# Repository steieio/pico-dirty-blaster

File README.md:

# Pico Dirty Blaster
USB Blaster adapters for [pico-dirtyJtag](https://github.com/phdussud/pico-dirtyJtag)
Also supports [Drag-n-Drop FPGA programming via UF2](https://steieio.github.io/pico-dirty-blaster/uf2jbc.html)
More documentation [available here](https://steieio.github.io/pico-dirty-blaster/)
You can purchase the PCB from [OSH Park](https://oshpark.com/)
 * [Through Hole PCB design at OSH Park](https://oshpark.com/shared_projects/5RjXdQ8y)

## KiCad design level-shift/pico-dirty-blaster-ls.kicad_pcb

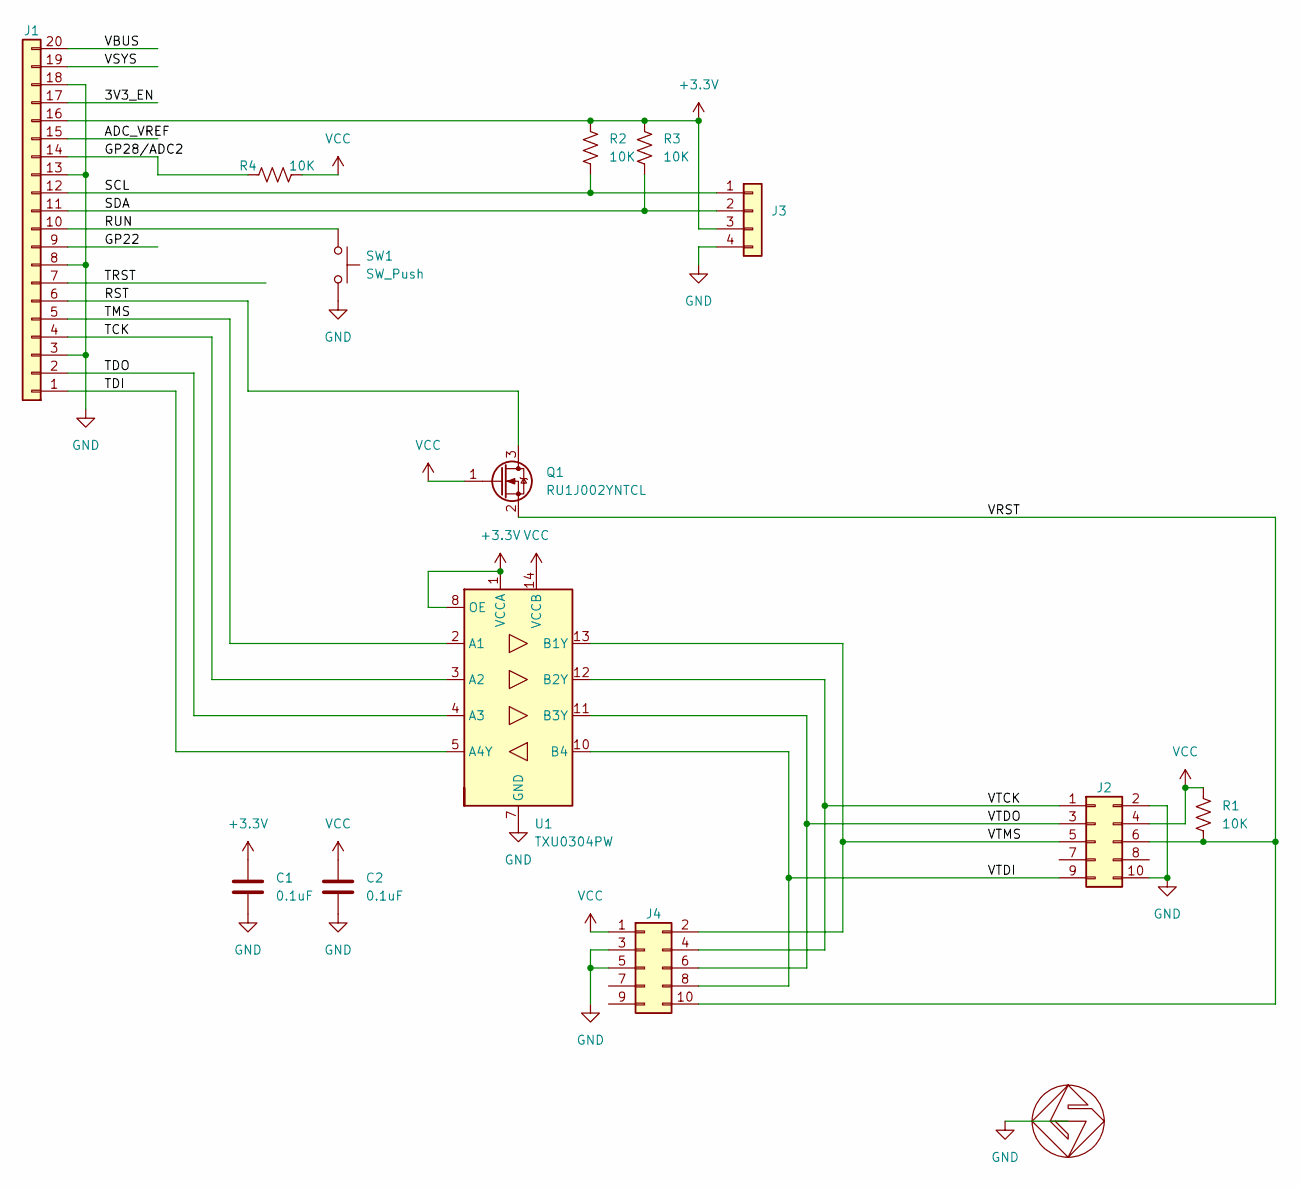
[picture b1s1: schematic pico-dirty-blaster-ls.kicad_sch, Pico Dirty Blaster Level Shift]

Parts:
C1, C2: 0.1uF; C_0603_1608Metric
GS1: GS_logo; gs_logo_200mil
J1: Conn_01x20; Sidecar-20
J2: Conn_02x05_Odd_Even; BHR-10-VSG-SMT_2x05_P2.54mm_Vertical_SMD
J3: Conn_01x04; JST_SH_SM04B-SRSS-TB_1x04-1MP_P1.00mm_Horizontal
J4: Conn_02x05_Odd_Even; PinHeader_2x05_P1.27mm_Vertical_SMD
Q1: RU1J002YNTCL; SOT-323_SC-70
R1, R2, R3, R4: 10K; R_0402_1005Metric
SW1: SW_Push; SW_Push_1P1T_NO_Vertical_Wuerth_434133025816
U1: TXU0304PW; TSSOP-14_4.4x5mm_P0.65mm

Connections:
+3.3V: C1.1, J1.16, J3.3, R2.1, R3.1, U1.1 (VCCA), U1.8 (OE)
/3V3_EN: J1.17
/ADC_VREF: J1.15
/GP22: J1.9
/GP28/ADC2: J1.14, R4.1
/RST: J1.6, Q1.3 (D)
/RUN: J1.10, SW1.1
/SCL: J1.12, J3.1, R2.2
/SDA: J1.11, J3.2, R3.2
/TCK: J1.4, U1.3 (A2)
/TDI: J1.1, U1.5 (A4Y)
/TDO: J1.2, U1.4 (A3)
/TMS: J1.5, U1.2 (A1)
/TRST: J1.7
/VBUS: J1.20
/VRST: J2.6, J4.10, Q1.2 (S), R1.2
/VSYS: J1.19
/VTCK: J2.1, J4.4, U1.12 (B2Y)
/VTDI: J2.9, J4.8, U1.10 (B4)
/VTDO: J2.3, J4.6, U1.11 (B3Y)
/VTMS: J2.5, J4.2, U1.13 (B1Y)
GND: C1.2, C2.2, GS1.1 (GS), J1.3, J1.8, J1.13, J1.18, J2.2, J2.10, J3.4, J4.3, J4.5, SW1.2, U1.7 (GND)
VCC: C2.1, J2.4, J4.1, Q1.1 (G), R1.1, R4.2, U1.14 (VCCB)

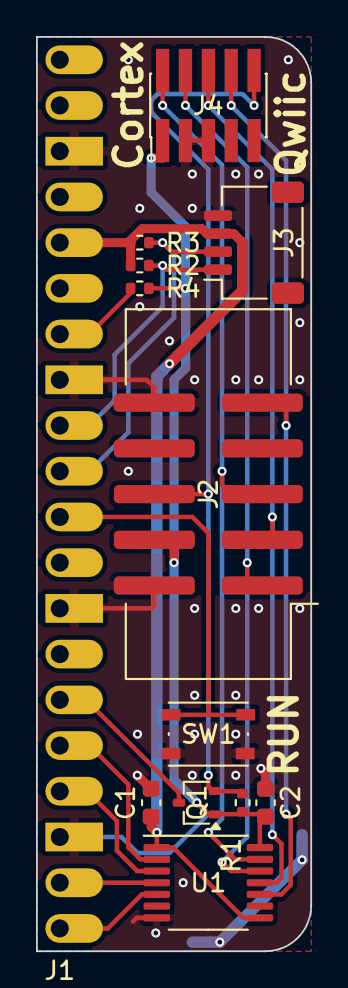
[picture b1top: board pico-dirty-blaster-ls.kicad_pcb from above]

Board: 2 copper layers, 15.2 x 50.8 mm, 14 parts (1 on the bottom side), 17 nets.

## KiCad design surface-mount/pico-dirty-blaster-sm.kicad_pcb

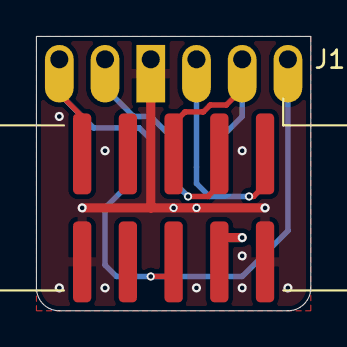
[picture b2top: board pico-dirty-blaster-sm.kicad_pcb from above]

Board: 2 copper layers, 15.2 x 15.2 mm, 3 parts (1 on the bottom side), 7 nets.

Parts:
J1: Conn_01x06; Sidecar-6
J2: Conn_02x05_Counter_Clockwise; PinHeader_2x05_P1.27mm_Vertical_SMD
J3: Conn_02x05_Counter_Clockwise; BHR-10-VSG-SMT_2x05_P2.54mm_Vertical_SMD

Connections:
/J_GND: J1.4, J2.3, J2.5, J3.2, J3.10
/J_RST: J1.1, J2.10, J3.6
/J_TCK: J1.3, J2.4, J3.1
/J_TDI: J1.6, J2.8, J3.9
/J_TDO: J1.5, J2.6, J3.3
/J_TMS: J1.2, J2.2, J3.5
/J_VCC: J2.1, J3.4

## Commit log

2024-05-01 initial rev 0.1 commit
2024-05-01 fix typo
2024-05-04 changed reset level shift to pass FET
2024-05-04 connected vcc on SM, 0402 R on LS
2024-05-06 fixed part number on level shifter
2024-05-31 added working pico-jbi.uf2 and uf2jbc.py pair
2024-05-31 added speed and options, plus cleaned up jbi and uf2jbc.py
2024-06-01 updated documentation
2024-06-01 cleaned up uf2jbc.md
2024-06-01 more details in documentation
2024-06-05 adding compiled dirtyJtag.uf2
